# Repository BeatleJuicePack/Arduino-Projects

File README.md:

# Arduino-Projects

This repository contains an assortment of projects based on the Arduino Uno.  
These projects are intended to be easy to practice while requiring little to no knowledge of programming and circuits.
Schematics created within Eagle are also available for review.

## Getting Started

Just clone/download the files and any dependencies for your project then upload to your matching circuit.

### Prerequisites

In order to run any Arduino based scripts you must first have an Arudino Uno as well as access to the Arduino IDE.
You can purchase an Arduino Uno or you can consider a starter kit at:
1. Arduino's website: https://store.arduino.cc/usa/arduino-uno-rev3
2. Amazon: https://www.amazon.com/Elegoo-EL-KIT-001-Project-Complete-Tutorial/dp/B01CZTLHGE/

The Arduino IDE can be downloaded from:
1. Arduino's website: https://www.arduino.cc/en/Main/Software
2. Arduino's online IDE: https://create.arduino.cc/editor
3. sudo apt-get install arduino
4. sudo yum install arduino

Occasionally scripts may require dependencies; in order to properly install them you can either:
1. Use Arduino's IDE Library Manager (available from IDE version 1.6.2 and up).
2. Search github repositories and clone/download the appropriate .zip for your project.  This can be done in a web browser or
thru the "git clone ssh://git@github.com/[username]/[repository-name].git	" command.  Once downloaded, import the library and
restart your IDE.

PCBs can easily be designed within Autodesk's Eagle PCB Design Software:
1. Visit Autodesk's website and make an account: https://www.autodesk.com/products/eagle/overview
2. Download, install, and open the schematic, or ".sch" files found within the repository.

### Example installation

1. Purchase a starter kit and learn the names of the various parts.
2. Download the Arduino IDE on Arduino's website.
3. Import any needed libraries specific to your project.
4. Clone the files from the repository.
5. Upload the code to your Arduino Uno.
6. Contribute to further developments.
7. Repeat as needed!

## Contributing

Please read [CONTRIBUTING.md](https://gist.github.com/BeatleJuicePack/47204bcc706e0e0c9e11d80e267f3d29) for details on our code of conduct, and the process
for submitting pull requests to us.

## Authors

* **BeatleJuice** - *Initial Work* - [BeatleJuicePack](https://github.com/BeatleJuicePack)
See also the list of [contributors](https://github.com/BeatleJuicePack/Arduino-Projects/contributors)

## License

This project is licensed under the GNU General Public License Version 3 - see the [LICENSE.md](LICENSE.md) file for details

## Acknowledgements

* A big thanks to any and all contributors, no matter how big or small the contribution it all helps.

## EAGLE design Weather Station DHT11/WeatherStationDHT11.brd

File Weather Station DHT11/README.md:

# Weather Station DHT11

This repository contains the plans to build an Arduino Uno Weather Station using a DHT11 Temperature & Humidity Sensor.  This
includes a single Photoresistor to analyze relative light levels and outputs the data on an LCD screen.

## Getting Started

Before you begin, make sure you have the necessary dependencies/libraries:
1. https://github.com/adafruit/Adafruit_Sensor
2. https://github.com/adafruit/DHT-sensor-library

*Note: You may need to rename files to contain only basic letters and numbers, no spaces.

**Note: When importing libraries on any previous versions of Arduino IDE prior to version 1.6.4 you must restart your IDE

### Items Required

1. Arduino Uno or similar device
2. DHT11 Module or similar device
3. LCD Module or similar device
4. Photoresistor
5. 10k ohm Resistor
6. 5k ohm Resistor
7. 10k ohm Potentiometer
8. a small Button
9. Breadboard or similar device
10. Jumper Cables or Soldering Equipment

## Circuit

1. The circuit can be viewed with file: [WeatherStationDHT11.png](WeatherStationDHT11.png)
2. Eagle schematics can be found in the file: [WeatherStationDTH11.sch](WeatherStationDHT11.sch)

## Issues
Currently the data within the repository can act as a prototype for learning about the Arduino Uno, however, the program is 
easily configurable to run consistently for long durations so long as issues are addressed such as:

1. Sleeping - the device is constantly on and will require a sleep-cycle in order to run for longer periods.
2. Dedicated PCB - this will reduce the overall power to the device and allow for a smaller, more manageable form factor.
3. Wireless connectivity - the Weather Station DHT11 can easily be modified to connect with an ESP8266 or similar device.
4. Cloud/Smart Home connectivity - connect to your Cloud/Smart Home and log data over long periods.
5. Battery/Solar Power - LiPo batteries and Solar Cells can easily be configured within the system.
6. Water/Weatherproofing - Due to the unpredictable nature of the outdoors, a Water or Weatherproof housing is needed.
7. Unknown variables - Let me know if you see any problems and/or solutions I did not mention here.
  
Assuming all the above issues are addressed and also assuming there is no the chance that more problems will arise in the 
future, the device will be capable of operating as an Open-Source Weather Station year-round.

## Contributing

Please read [CONTRIBUTING.md](https://gist.github.com/BeatleJuicePack/47204bcc706e0e0c9e11d80e267f3d29) for details on our
code of conduct, and the process for submitting pull requests to us.

## Authors

* **BeatleJuice** - *Initial Work* - [BeatleJuicePack](https://github.com/BeatleJuicePack)
See also the list of [contributors](https://github.com/BeatleJuicePack/Arduino-Projects/contributors)

## License

This project is licensed under the GNU General Public License Version 3 - see the [LICENSE.md](LICENSE.md) file for details

## Acknowledgements

* A big thanks to any and all contributors, no matter how big or small the contribution it all helps.

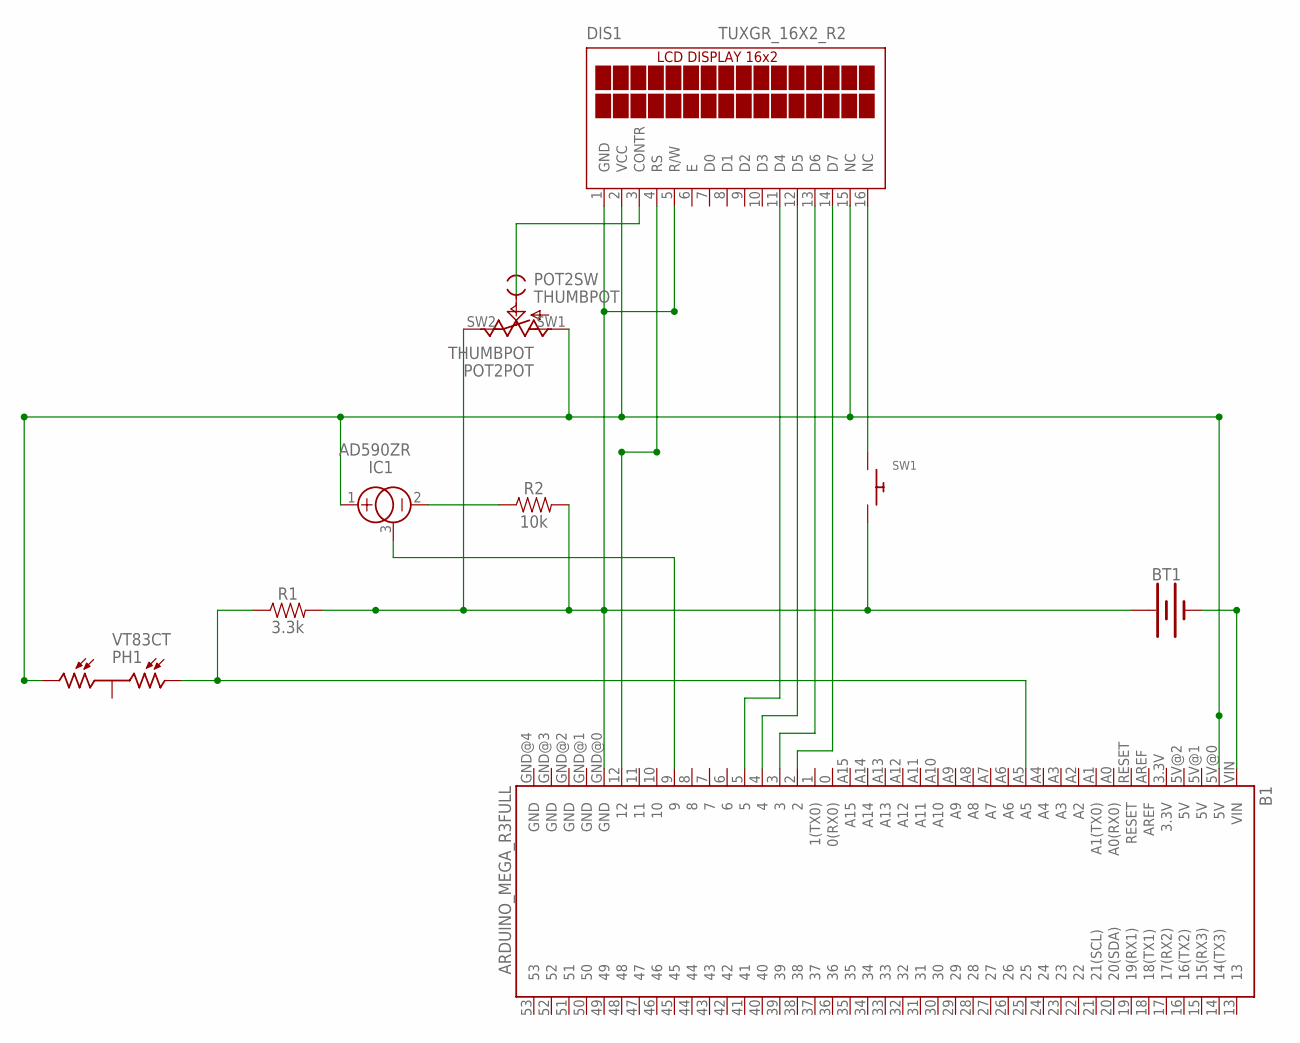
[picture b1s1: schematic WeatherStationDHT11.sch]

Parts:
B1: ARDUINO_MEGA_R3FULL; ARDUINO_MEGA
BT1: BATTERY-9V; BATTCON_9V
DIS1: TUXGR_16X2_R2
IC1: AD590ZR; TO92
PH1: VT83CT; VT800CT
POT2: THUMBPOT; THUMBWHEEL
R1: 3.3k; 0603
R2: 10k; 0603
SW1: SWITCH_PUSHBUTTONC&K_KSS; BTN_CK_KSS

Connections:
unnamed: B1.VIN, BT1.-
unnamed: B1.A5, PH1.1, R1.1
unnamed: IC1.2 (-), R2.1
unnamed: B1.5V@0 (5V), DIS1.2 (VCC), DIS1.15 (NC), IC1.1 (+), PH1.3, POT2.1 (A)
unnamed: B1.GND@0 (GND), BT1.+, DIS1.1 (GND), DIS1.5 (R/W), POT2.3 (E), R1.2, R2.2, SW1.P$2
unnamed: B1.9, IC1.3 (CAN)
unnamed: B1.5, DIS1.11 (D4)
unnamed: B1.12, DIS1.4 (RS)
unnamed: B1.4, DIS1.12 (D5)
unnamed: DIS1.3 (CONTR), POT2.2 (S)
unnamed: B1.3, DIS1.13 (D6)
unnamed: B1.2, DIS1.14 (D7)
unnamed: DIS1.16 (NC), SW1.P$1

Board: 2 copper layers, 9 parts (0 on the bottom side), 13 nets, no tracks yet.

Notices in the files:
parts and their libraries:
SparkFun-Boards: Licensing: Creative Commons ShareAlike 4.0 International - https://creativecommons.org/licenses/by-sa/4.0
